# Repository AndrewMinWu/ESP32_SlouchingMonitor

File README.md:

# Laptop Slouching Monitor

## Repository Structure

```text
├── hardware/          # Schematic, PCB, and gerbers
├── firmware/          # PlatformIO C++ code, and Python script
└── docs/              # Datasheets
```

## Purpose & Motivation:
Spending long hours working at a computer, I noticed my posture deteriorating as I constantly leaned closer to the monitor. Over time, this habit leads to back pain and eye strain (probably why my eyesight is so bad). Therefore, to prevent future issues and to force myself to build better sitting habits, I designed a PCB using an ESP32 and a Time-of-Flight (ToF) sensor to accurately monitor my distance from the screen and trigger a desktop popup whenever I slouch.

## Design

### Component List (BOM)
1. ESP32-C3-WROOM-02 ([Datasheet](https://www.espressif.com/sites/default/files/documentation/esp32-c3-wroom-02_datasheet_en.pdf))
2. AP2112K-3.3 LDO Voltage Regulator ([Datasheet](https://www.diodes.com/assets/Datasheets/AP2112.pdf))
3. GCT USB4105-GF-A USB-C Receptacle 16P SMD RA ([Datasheet](https://gct.co/files/drawings/usb4105.pdf))
4. VL53L0X Time-of-Flight Distance Sensor ([Datasheet](https://www.st.com/resource/en/datasheet/vl53l0x.pdf))
5. Passives & Miscellaneous Hardware:
   - Capacitors (0805, Ceramic)
   - Resistors (0805)
   - Push Buttons

### PCB, Schematic, Finished Board
The Schematic and PCB were designed in KiCad.

<table width="100%">
  <tr>
    <td width="50%"></td>
    <td width="50%"></td>

  </tr>
</table>

### Firmware & Software
* **Language & Framework:** C++ (Arduino IDE) and Python, done using VSCode with PlatformIO
* **I2C Configuration:** GPIO 0 (SDA), GPIO 1 (SCL)
* **Desktop Application:** Python script using pyserial and tkinter for the popup alerts

## Assembly & Demonstration

**Short Demo**  
<video src="https://github.com/user-attachments/assets/37af02e7-89a8-4d62-8e1a-ba28e2ae51d5" width="100%" controls></video>

* **Assembly:** Hand-soldered all parts and tested the board with a multimeter (checking continuity with the implemented testpoints) before flashing firmware.

## Active Development

* **Enclosure:** 3D printing a case to mount the PCB to the top of my monitor, using Fusion 360

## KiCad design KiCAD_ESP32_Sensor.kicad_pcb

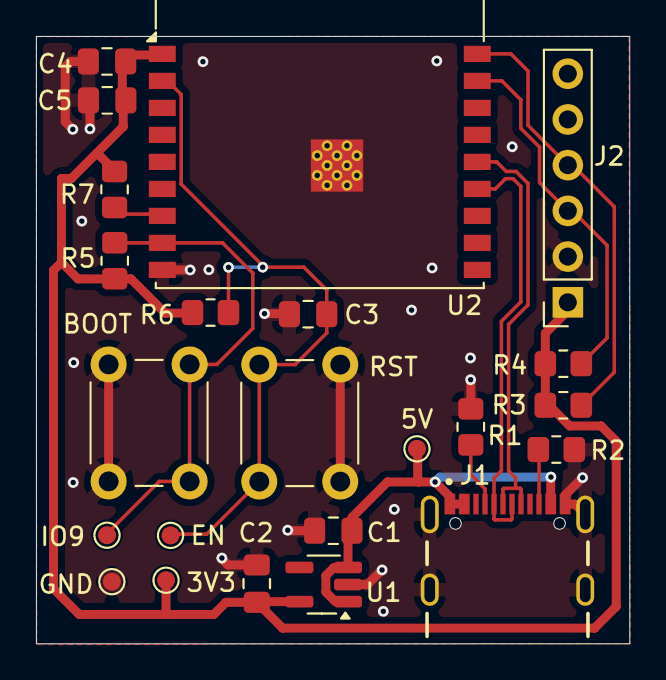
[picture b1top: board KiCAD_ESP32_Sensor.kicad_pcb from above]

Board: 2 copper layers, 33.0 x 33.7 mm, 23 parts (0 on the bottom side), 12 nets.

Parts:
3V3: 3.3V; TestPoint_Pad_D1.0mm
5V: 5V; TestPoint_Pad_D1.0mm
BOOT: SW_Push; SW_PUSH_6mm_H5mm
C1, C2, C3: 1u; C_0805_2012Metric_Pad1.18x1.45mm_HandSolder
C4: 0.1u; C_0805_2012Metric_Pad1.18x1.45mm_HandSolder
C5: 10u; C_0805_2012Metric_Pad1.18x1.45mm_HandSolder
EN: EN; TestPoint_Pad_D1.0mm
GND: GND; TestPoint_Pad_D1.0mm
IO9: IO0; TestPoint_Pad_D1.0mm
J1: USB_C_Receptacle_USB2.0_16P; GCT_USB4105-GF-A
J2: VL53L0X_Module; PinSocket_1x06_P2.54mm_Vertical
R1, R2: 5.1k; R_0805_2012Metric_Pad1.20x1.40mm_HandSolder
R3, R4: 4.7k; R_0805_2012Metric_Pad1.20x1.40mm_HandSolder
R5, R6, R7: 10k; R_0805_2012Metric_Pad1.20x1.40mm_HandSolder
RST: SW_Push; SW_PUSH_6mm_H5mm
U1: AP2112K-3.3; SOT-23-5_HandSoldering
U2: ESP32-C3-WROOM-02

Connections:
+3.3V: 3V3.1 (1_1), C2.1, C4.1, C5.1, J2.1, R3.2, R4.2, R5.1, R6.1, R7.1, U1.5 (VOUT), U2.1 (3V3)
+5V: 5V.1 (1_1), C1.1, J1.A1_B12 (VBUS_B9), J1.A4_B9 (VBUS_B4), J1.B4_A9 (VBUS_A4), U1.1 (VIN), U1.3 (EN)
D+: J1.A6 (D+_A6), J1.B6 (D+_B6), U2.14 (IO19)
D-: J1.A7 (D-_A7), J1.B7 (D-_B7), U2.13 (IO18)
EN: C3.2, EN.1 (1_1), R6.2, RST.1, U2.2 (EN)
GND: BOOT.2, C1.2, C2.2, C3.1, C4.2, C5.2, GND.1 (1_1), J1.B1_A12 (GND_A12), J1.SH1 (SHIELD_SH), J1.SH2 (SHIELD_SH), J1.SH3 (SHIELD_SH), J1.SH4 (SHIELD_SH), J2.2, R1.1, R2.1, RST.2, U1.2 (GND), U2.9 (GND), U2.19 (GND)
IO9: BOOT.1, IO9.1 (1_1), R5.2, U2.8 (IO9)
unnamed: J1.A5 (CC1_A5), R1.2
unnamed: J1.B5 (CC2_B5), R2.2
unnamed: R7.2, U2.7 (IO8)
SCL: J2.3, R4.1, U2.17 (IO1)
SDA: J2.4, R3.1, U2.18 (IO0)
